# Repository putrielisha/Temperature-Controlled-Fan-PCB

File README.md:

# Temperature-Controlled-Fan-PCB
Temperature-controlled fan system implemented using a custom PCB designed in Autodesk EAGLE and embedded C firmware for real-time thermal regulation.

# Overview
This project is a microcontroller-based temperature-controlled cooling system designed using a custom PCB created in Autodesk EAGLE. The system reads real-time temperature data and automatically controls a USB fan based on a defined threshold using embedded C firmware.

# Features
- Real-time temperature monitoring via ADC
- Automatic fan ON/OFF control based on threshold value
- Custom PCB designed using Autodesk EAGLE
- Embedded C firmware for microcontroller logic
- USB-powered fan output control

# System Workflow
Temperature sensor → Microcontroller → Threshold comparison → GPIO output → Fan control

# Hardware Design
- Custom PCB designed using Autodesk EAGLE
- Fabricated through an external PCB manufacturing company arranged by the school
- Microcontroller-based control system for temperature monitoring and fan actuation
- USB-powered output stage for fan control

# Firmware
The firmware was developed in C (Microchip Studio) and handles:
- ADC-based temperature reading
- Conversion of sensor values into temperature
- Comparison against preset threshold values
- GPIO-based fan control output

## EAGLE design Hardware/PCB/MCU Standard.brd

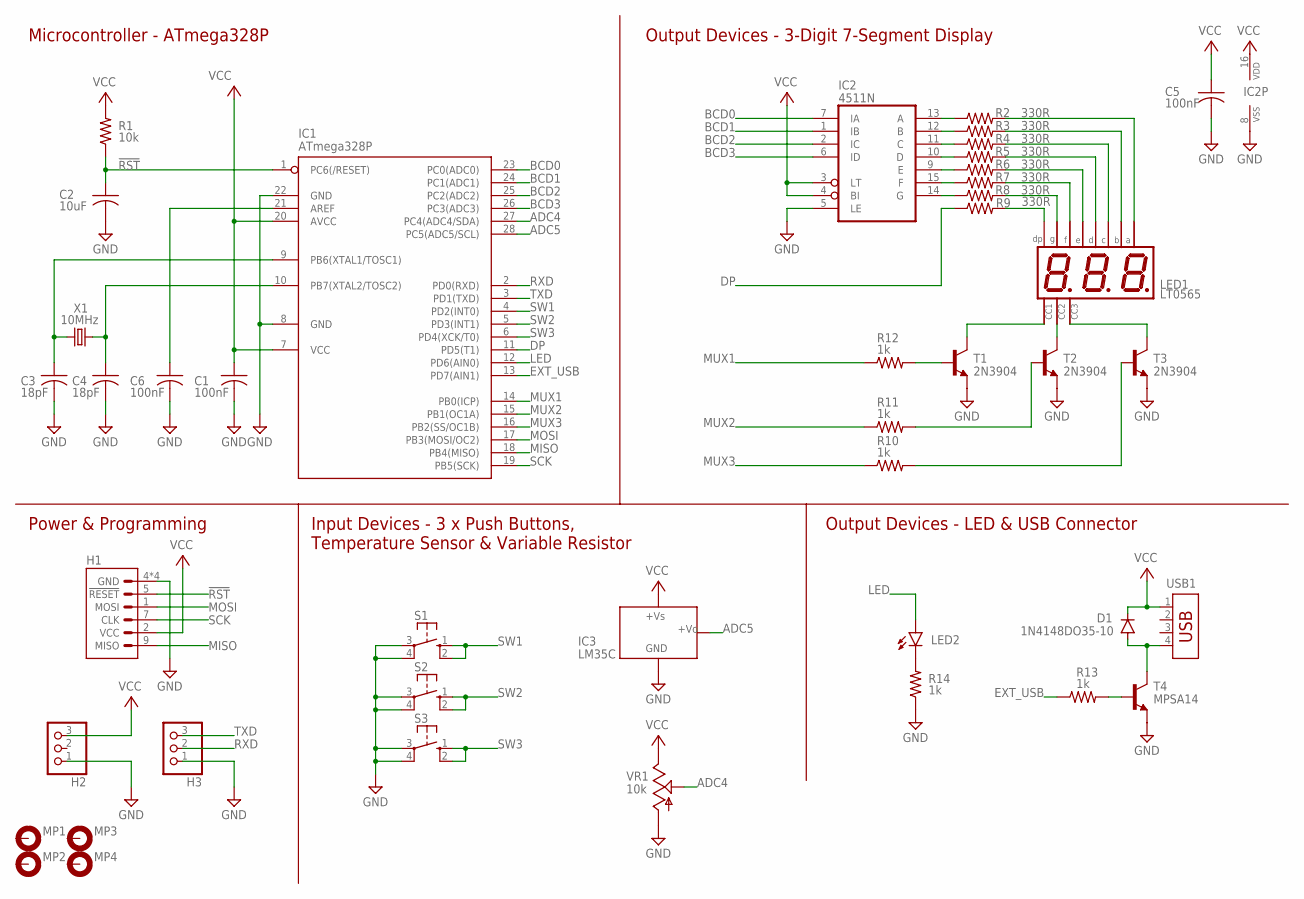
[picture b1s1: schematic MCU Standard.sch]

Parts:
C1, C5, C6: 100nF; C050-024X044
C2: 10uF; C050-024X044
C3, C4: 18pF; C050-024X044
D1: 1N4148DO35-10; DO35-10
H1: MISO_MOSI_IPC-10V; IDC-10V
H2, H3: PINHD-1X03_2.54-90°; 1X03/90
IC1: ATmega328P; DIL28-3
IC2: 4511N; DIL16
IC3: LM35C; TO92
LED1: LT0565; BX56/BX55
LED2: LED3MM
MP1, MP2, MP3, MP4: MOUNT-PAD-ROUND3.2; 3,2-PAD
R1: 10k; 0207/10
R2, R3, R4, R5, R6, R7, R8, R9: 330R; 0207/10
R10, R11, R12, R13, R14: 1k; 0207/10
S1, S2, S3: 10-XX; B3F-10XX
T1, T2, T3: 2N3904; TO92
T4: MPSA14; TO92
USB1: USB-787616; USB
VR1: 10k; PT-10
X1: 10MHz; HC49/S

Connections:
!RST: C2.1, H1.5 (!RESET), IC1.1 (PC6(/RESET)), R1.1
ADC4: IC1.27 (PC4(ADC4/SDA)), VR1.3 (S)
ADC5: IC1.28 (PC5(ADC5/SCL)), IC3.2 (VO)
BCD0: IC1.23 (PC0(ADC0)), IC2.7 (IA)
BCD1: IC1.24 (PC1(ADC1)), IC2.1 (IB)
BCD2: IC1.25 (PC2(ADC2)), IC2.2 (IC)
BCD3: IC1.26 (PC3(ADC3)), IC2.6 (ID)
DP: IC1.11 (PD5(T1)), R9.1
EXT_USB: IC1.13 (PD7(AIN1)), R13.1
GND: C1.2, C2.2, C3.2, C4.2, C5.2, C6.2, H1.4 (GND), H1.6 (GND), H1.8 (GND), H1.10 (GND), H2.1, H3.1, IC1.8 (GND), IC1.22 (GND), IC2.5 (LE), IC2.8 (VSS), IC3.1 (GND), R14.1, S1.3, S1.4 (P1), S2.3, S2.4 (P1), S3.3, S3.4 (P1), T1.3 (E), T2.3 (E), T3.3 (E), T4.3 (E), VR1.1 (A)
LED: IC1.12 (PD6(AIN0)), LED2.A
MISO: H1.9 (MISO), IC1.18 (PB4(MISO))
MOSI: H1.1 (MOSI), IC1.17 (PB3(MOSI/OC2))
MUX1: IC1.14 (PB0(ICP)), R12.1
MUX2: IC1.15 (PB1(OC1A)), R11.1
MUX3: IC1.16 (PB2(SS/OC1B)), R10.1
unnamed: C3.1, IC1.9 (PB6(XTAL1/TOSC1)), X1.1
unnamed: C4.1, IC1.10 (PB7(XTAL2/TOSC2)), X1.2
unnamed: LED1.5 (G), R8.2
unnamed: LED1.10 (F), R7.2
unnamed: LED1.1 (E), R6.2
unnamed: LED1.2 (D), R5.2
unnamed: LED1.4 (C), R4.2
unnamed: LED1.7 (B), R3.2
unnamed: LED1.11 (A), R2.2
unnamed: IC2.13 (A), R2.1
unnamed: IC2.12 (B), R3.1
unnamed: IC2.11 (C), R4.1
unnamed: IC2.10 (D), R5.1
unnamed: IC2.9 (E), R6.1
unnamed: IC2.15 (F), R7.1
unnamed: IC2.14 (G), R8.1
unnamed: LED1.3 (DP), R9.2
unnamed: C6.1, IC1.21 (AREF)
unnamed: LED1.8 (CA), T3.1 (C)
unnamed: LED1.9 (CA), T2.1 (C)
unnamed: LED1.12 (CA), T1.1 (C)
unnamed: R10.2, T3.2 (B)
unnamed: R11.2, T2.2 (B)
unnamed: R12.2, T1.2 (B)
unnamed: R13.2, T4.2 (B)
unnamed: D1.A, T4.1 (C), USB1.4
unnamed: LED2.K (C), R14.2
RXD: H3.2, IC1.2 (PD0(RXD))
SCK: H1.7 (CLK), IC1.19 (PB5(SCK))
SW1: IC1.4 (PD2(INT0)), S1.1 (S), S1.2 (S1)
SW2: IC1.5 (PD3(INT1)), S2.1 (S), S2.2 (S1)
SW3: IC1.6 (PD4(XCK/T0)), S3.1 (S), S3.2 (S1)
TXD: H3.3, IC1.3 (PD1(TXD))
VCC: C1.1, C5.1, D1.C, H1.2 (VCC), H2.3, IC1.7 (VCC), IC1.20 (AVCC), IC2.3 (LT), IC2.4 (BI), IC2.16 (VDD), IC3.3 (+VS), R1.2, USB1.1, VR1.2 (E)

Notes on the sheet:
Power & Programming
Input Devices - 3 x Push Buttons, Temperature Sensor & Variable Resistor
Output Devices - LED & USB Connector
Output Devices - 3-Digit 7-Segment Display
Microcontroller - ATmega328P

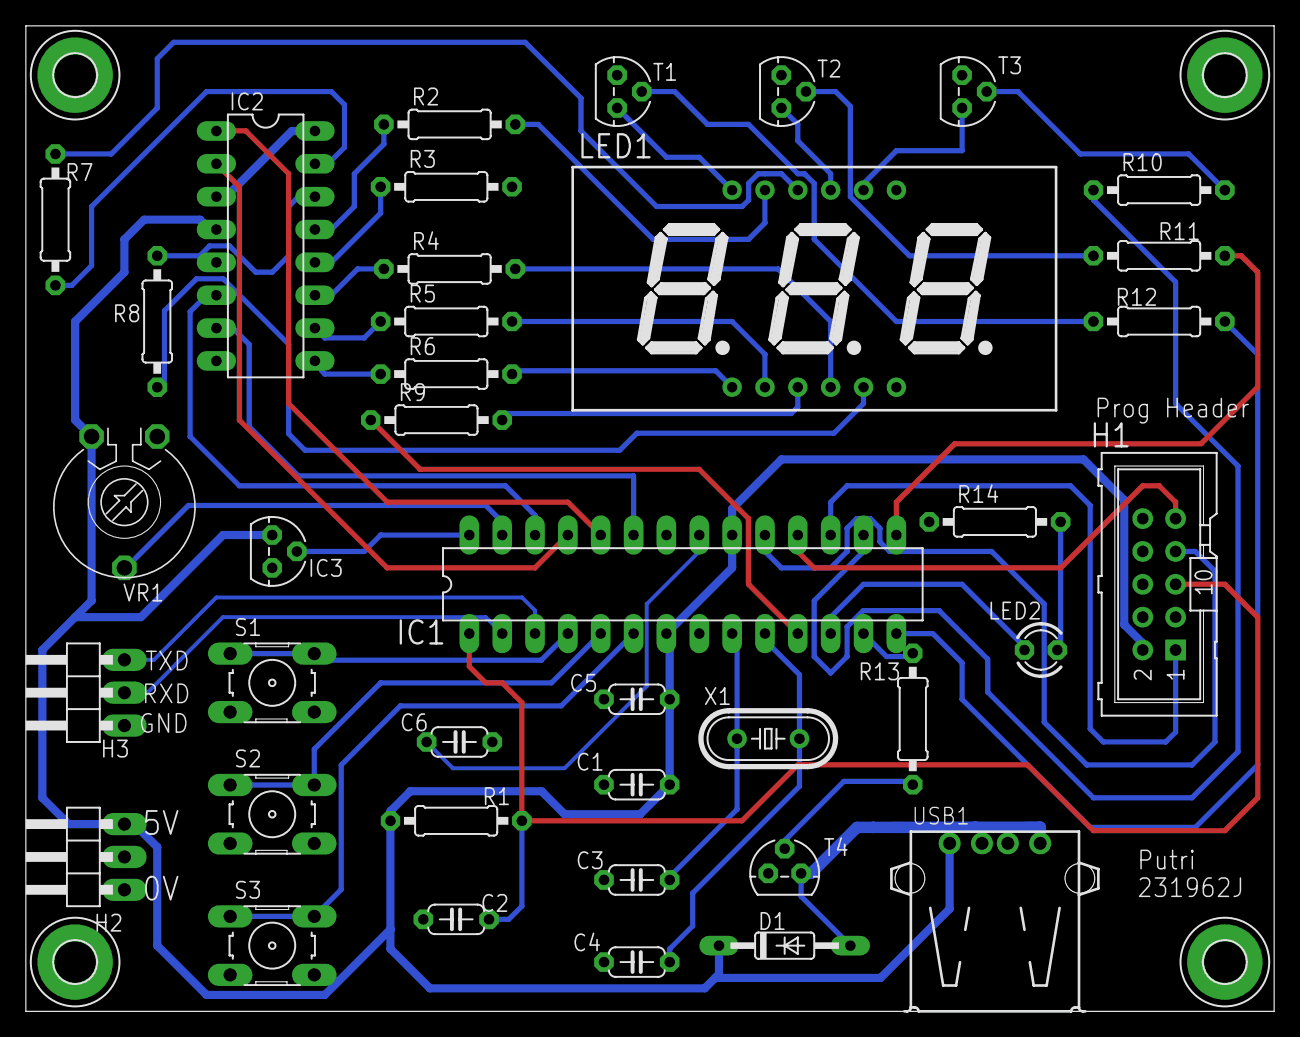
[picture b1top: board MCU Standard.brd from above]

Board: 2 copper layers, 96.5 x 76.2 mm, 43 parts (0 on the bottom side), 50 nets.

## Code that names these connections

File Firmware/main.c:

#include <avr/io.h>
#include <avr/interrupt.h>
#define TurnOnTemp 26
#define TurnOffTemp 25

void delay(unsigned long k){	//delay function with argument
	while(--k!=0);
}

void display(unsigned int num){	//function to display num value at 3-digit 7 seg display
	unsigned char a,b,c,x;
	a = num/100;	//split num into 3 individual digit a,b,c using formulae
	b = (num%100)/10;
	c = num%10;
	for(x=0;x<100;x++){
		PORTB = (PORTB & 0xF8)| 0x01;	//on left digit
		PORTC = (PORTC & 0xF0)| a;	//display value a at left digit
		delay(100);
		PORTB = (PORTB & 0xF8)| 0x02;	//on middle digit
		PORTC = (PORTC & 0xF0)| b;	//display value b at middle digit
		delay(100);
		PORTB = (PORTB & 0xF8)| 0x04;	//on right digit
		PORTC = (PORTC & 0xF0)| c;	//display value c in right digit
		delay(100);
	}
}

void ADC_Init(){
	DIDR0 = 0x20; // Disable digital.
	DDRC = DDRC & ~(0x20);	//PC5=Input.
	PORTC = PORTC & ~(0x30);	// Enable ADC & set clock.
	ADCSRA |= 0x87;
	ADMUX = 0xC0; //Vref=1.1V
}

unsigned int ADC_Read(){	// Select PC5 as input.
	ADMUX = (ADMUX & 0xF0) | 0x05;
	ADCSRA |= 0x40; // Start ADC.
	while ((ADCSRA & 0x10)==0); //Wait.
	ADCSRA |= 0x10; // Reset.
	return ADCW;
}

int convert(unsigned int adcValue){
	unsigned long c;
	c = (long) adcValue * 1075;	//multiply 1075
	adcValue = c/1000;	//divide by 1000
	return(adcValue);	//adcValue is converted to measured temp & return to calling function
}

// ||EXPERIMENTAL||
// int main(){
// 	unsigned int adcValue;
// 	DDRC |= 0x0F; // Configure output.
// 	DDRB |= 0x07; // Configure output.
// 	DDRD |= 0x80;
// 	ADC_Init();
// 	while(1){
// 		adcValue = ADC_Read();
// 		display(adcValue);
// 	}
//
unsigned int dpNum;
unsigned char whichDigit=1, subSec=0;

void delay2(unsigned long w){
	while(w--!=0);
}

// ||EXPERIMENTAL INTERRUPT||
// ISR(TIMER0_OVF_vect) {
// 	unsigned char digit;
// 	TCNT0 = 0x81;	//set 5msec timer
// 	subSec++;
// 	if (subSec==200){
// 		subSec=0;
// 		dpNum++;
// 		if (dpNum>999) dpNum=0;
// 	}
// 	switch(whichDigit){
// 		case 1: digit = dpNum/100;
// 		PORTB = (PORTB & 0xf8)| 0x01;
// 		PORTC = (PORTC & 0XF0)| digit;
// 		break;
// 		case 2: digit = (dpNum%100)/10;
// 		PORTB = (PORTB & 0xf8)| 0x02;
// 		PORTC = (PORTC & 0XF0)| digit;
// 		break;
// 		case 3: digit = dpNum%10;
// 		PORTB = (PORTB & 0xf8)| 0x04;
// 		PORTC = (PORTC & 0XF0)| digit;
// 		break;
// 	}
// 	whichDigit++;
// 	if (whichDigit>3) whichDigit=1;
// }
// 
// void initTimer0(){
// 	TCNT0 = 0x81; // set 0.5s timer
// 	TIFR0 |= 0x01; // Clear Overflow Flag.
// 	TCCR0B = (TCCR0B & 0xF8)| 0x05;	// Start timer.
//
// ||EXPERIMENTAL||
// int main2(void)
// {
// 	DDRC = 0x0F;	//set PC0-PC3 as output, PC4-PC7 as input
// 	DDRB = 0x07;	//Set PB0-PB2 as output for MUX1, MUX2 & MU3
// 	DDRD = 0x80;
// 	TIMSK0 |= 0x01;	// Enable Timer 1 Interrupt
// 	sei();
// 	initTimer0();
// 	while(1){	//do nothing
// 	}
// }

int main(void) {
	unsigned int adcValue;
	DDRC |= 0x0F; // Configure PC0-PC3 as output
	DDRB |= 0x07; // Configure PB0-PB3 as output
	DDRD |= 0x80;
	ADC_Init();
	while (1){
		adcValue = ADC_Read();
		int temperature = convert(adcValue);
		display(temperature);
		if (temperature >= TurnOnTemp) {
			PORTD |= 0x08; // Turn on fan (PB3 = High, 0x08)
			} else if (temperature <= TurnOffTemp) {
			PORTD &= ~0x08; // Turn off fan (PB3 = Low, 0x08)
		}
	}
}
